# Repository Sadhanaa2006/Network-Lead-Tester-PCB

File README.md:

**🔌 Network Lead Tester PCB Design**

**📖 Overview**

This project presents the PCB layout design of a Network Lead Tester using the NE555 Timer and CD4017 Decade Counter. The circuit is designed to verify the continuity and correct wiring sequence of RJ45 Ethernet cables through sequential LED indication.

The PCB layout was designed using Autodesk EAGLE, including component placement, manual trace routing, and board organization based on the provided schematic.

**✨ Features**

- Single-layer PCB layout
- RJ45 Ethernet cable testing
- Sequential LED indication
- Manual component placement
- Manual bottom-layer routing
- Through-hole PCB design

**⚙️ Working Principle**

- The **NE555 Timer** operates in astable mode to generate clock pulses.
- The **CD4017 Decade Counter** receives these pulses and activates one output at a time.
- Both ends of an **RJ45 Ethernet cable** are connected to the tester.
- If the cable is wired correctly, the LEDs illuminate sequentially from **1 → 8**.
- Any open circuit, crossed pair, or incorrect wiring changes the LED sequence, allowing faults to be identified quickly.

**🛠️ Components Used**

- NE555 Timer IC
- CD4017 Decade Counter IC
- RJ45 Connectors
- LEDs
- Resistors
- Capacitors
- 9V Battery Connector

**💻 Software Used**

- Autodesk EAGLE

**🎯 Skills Demonstrated**

- PCB Layout Design
- Schematic Interpretation
- Component Placement
- Manual PCB Routing
- Through-Hole PCB Design
- PCB Documentation

**🎯 Applications**

- Ethernet (LAN) cable testing
- RJ45 wiring verification
- Network cable continuity testing
- Educational electronics and networking projects

**📌 Note**

The circuit schematic was provided as part of a PCB design exercise. This project demonstrates the PCB layout development process, including component placement and manual routing using Autodesk EAGLE.

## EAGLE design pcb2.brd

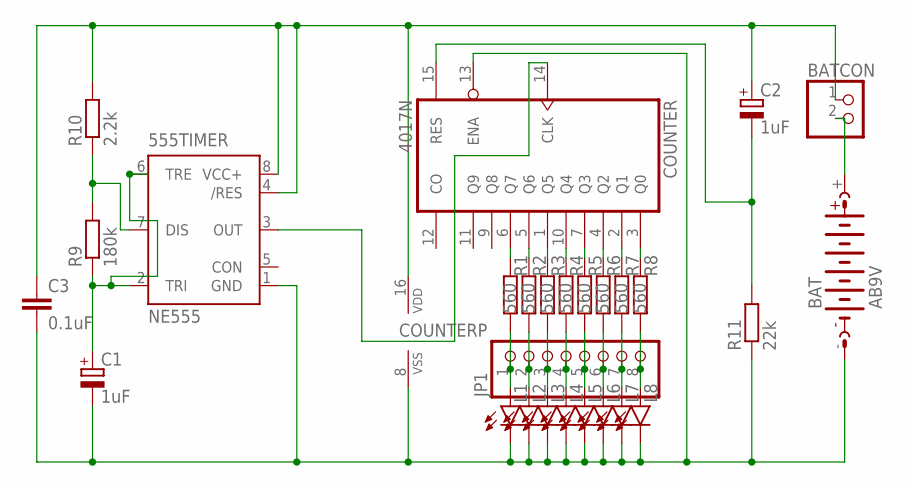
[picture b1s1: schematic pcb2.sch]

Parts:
555TIMER: NE555; DIL-08
BAT: AB9V
BATCON: PINHD-1X2; 1X02
C1, C2: 1uF; E2,5-5
C3: 0.1uF; C050-024X044
COUNTER: 4017N; DIL16
JP1: PINHD-1X8; 1X08
L1, L2, L3, L4, L5, L6, L7, L8: LED5MM
R1, R2, R3, R4, R5, R6, R7, R8: 560; 0207/10
R9: 180k; 0207/10
R10: 2.2k; 0207/10
R11: 22k; 0207/10

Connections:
unnamed: JP1.2, L2.A, R2.1
unnamed: COUNTER.2 (Q1), R7.2
unnamed: C2.-, COUNTER.15 (RES), R11.2
unnamed: BAT.+, BATCON.2
unnamed: 555TIMER.3 (OUT), COUNTER.14 (CLK)
unnamed: 555TIMER.4 (/RES), 555TIMER.8 (VCC+), BATCON.1, C2.+, C3.1, COUNTER.16 (VDD), R10.2
unnamed: 555TIMER.1 (GND), BAT.-, C1.-, C3.2, COUNTER.8 (VSS), COUNTER.13 (ENA), L1.K (C), L2.K (C), L3.K (C), L4.K (C), L5.K (C), L6.K (C), L7.K (C), L8.K (C), R11.1
unnamed: 555TIMER.7 (DIS), R9.2, R10.1
unnamed: COUNTER.6 (Q7), R1.2
unnamed: COUNTER.5 (Q6), R2.2
unnamed: 555TIMER.2 (TRI), 555TIMER.6 (TRE), C1.+, R9.1
unnamed: COUNTER.1 (Q5), R3.2
unnamed: COUNTER.7 (Q3), R5.2
unnamed: COUNTER.4 (Q2), R6.2
unnamed: COUNTER.3 (Q0), R8.2
unnamed: JP1.1, L1.A, R1.1
unnamed: JP1.5, L5.A, R5.1
unnamed: JP1.3, L3.A, R3.1
unnamed: COUNTER.10 (Q4), R4.2
unnamed: JP1.6, L6.A, R6.1
unnamed: JP1.7, L7.A, R7.1
unnamed: JP1.8, L8.A, R8.1
unnamed: JP1.4, L4.A, R4.1

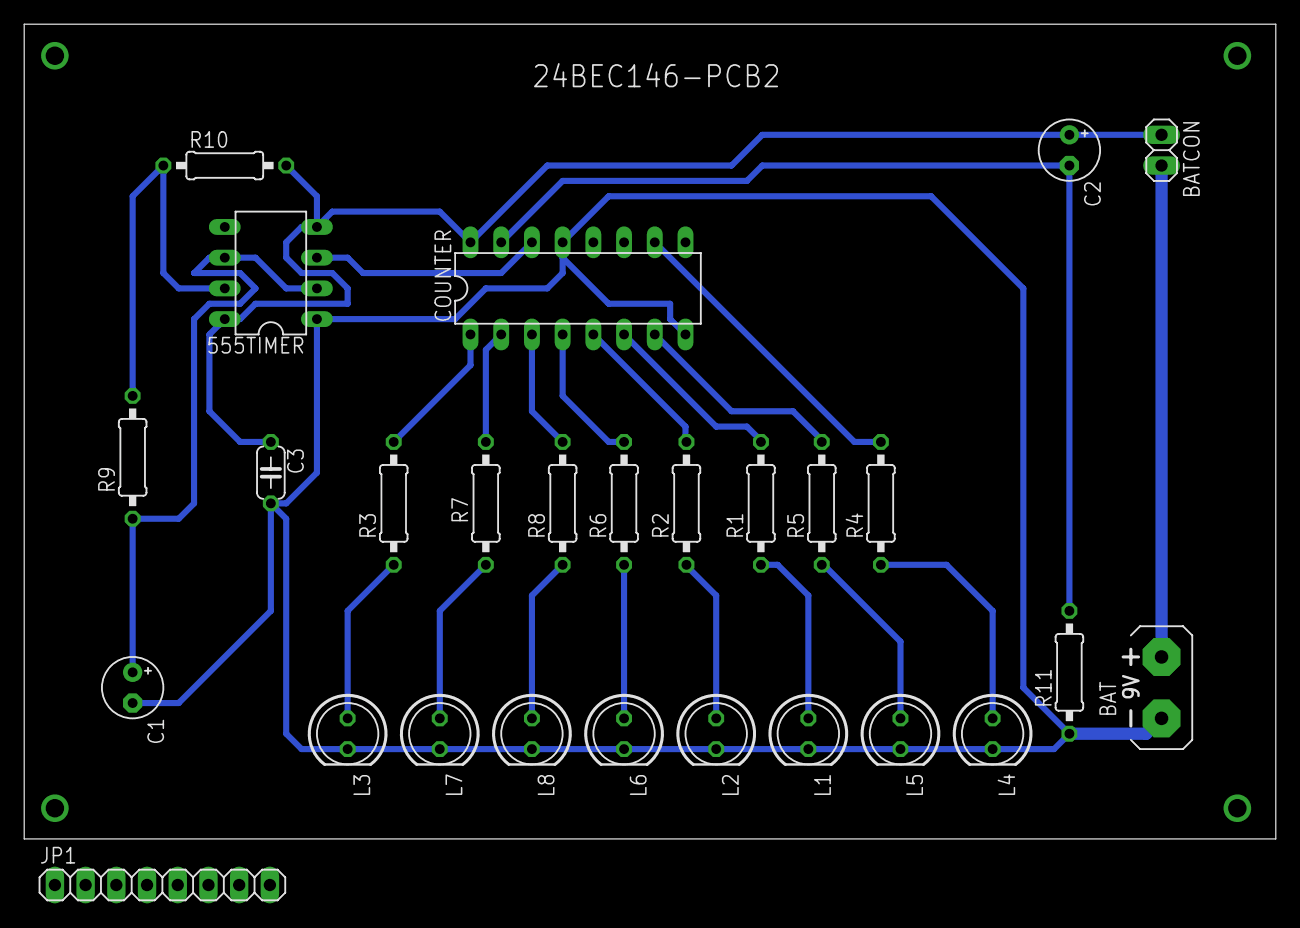
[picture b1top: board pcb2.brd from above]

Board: 2 copper layers, 103.5 x 67.4 mm, 27 parts (0 on the bottom side), 23 nets.

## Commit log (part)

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2026-06-19 Rename Bottom-layer.png to Images/Bottom-layer.png
2026-06-19 Rename PCB-design.png to Images/PCB-design.png
2026-06-19 Rename Top-layer.png to Images/Top-layer.png
2026-06-19 Rename Schematic.png to Images/Schematic.png
